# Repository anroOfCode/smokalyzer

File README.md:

smokalyzer
==========
Code and design files for a headset-connected device that can detect if you've been smoking.

Info
====
This project is based on the HiJack platform. It includes an interface board designed for use with an electrochemical gas sensor, 3D design files for the creation of an enclosure, and code for iOS and for the HiJack platform that allows for reading and calibration.

What You'll Find Here
=====================

Code for Use With TinyOS
------------------------
Code has been written to be used with the HiJack platform, installed with TinyOS. TinyOS is difficult to setup, but the process should look something like this:

- Check out version 2.1.1 from the TinyOS Subversion page
- Install it on your local machine, including tos-tools. (see documentation on their site)
- Check out the hijack-main code from the google code project and copy the directory structure such that it matches up with your tinyos main folder
- Build the apps using 'make hijack install miniprog bsl,/dev/ttyUSB0'

An iOS App That Displays CO Data
--------------------------------
This is one of my very, very first endeavors into iOS app making. The code is not clean but will hopefully be cleaned up over time. We've imported libHiJack from the HiJack project as well, which requires delicacy when it comes to using ARC. The app supports basic calibration and reading of the instrument. 

Board Design Files
------------------
The files will allow you to order more of the PCB. They have been produced using Eagle 6.3.0.

Enclosure Design Files
----------------------
These files can serve as a starting point for a professional enclosure. They can also be 3D prototyped by any 3D lab for prototype enclosures. 

Questions?
==========
Feel free to contact me with questions. Responses are not guaranteed.

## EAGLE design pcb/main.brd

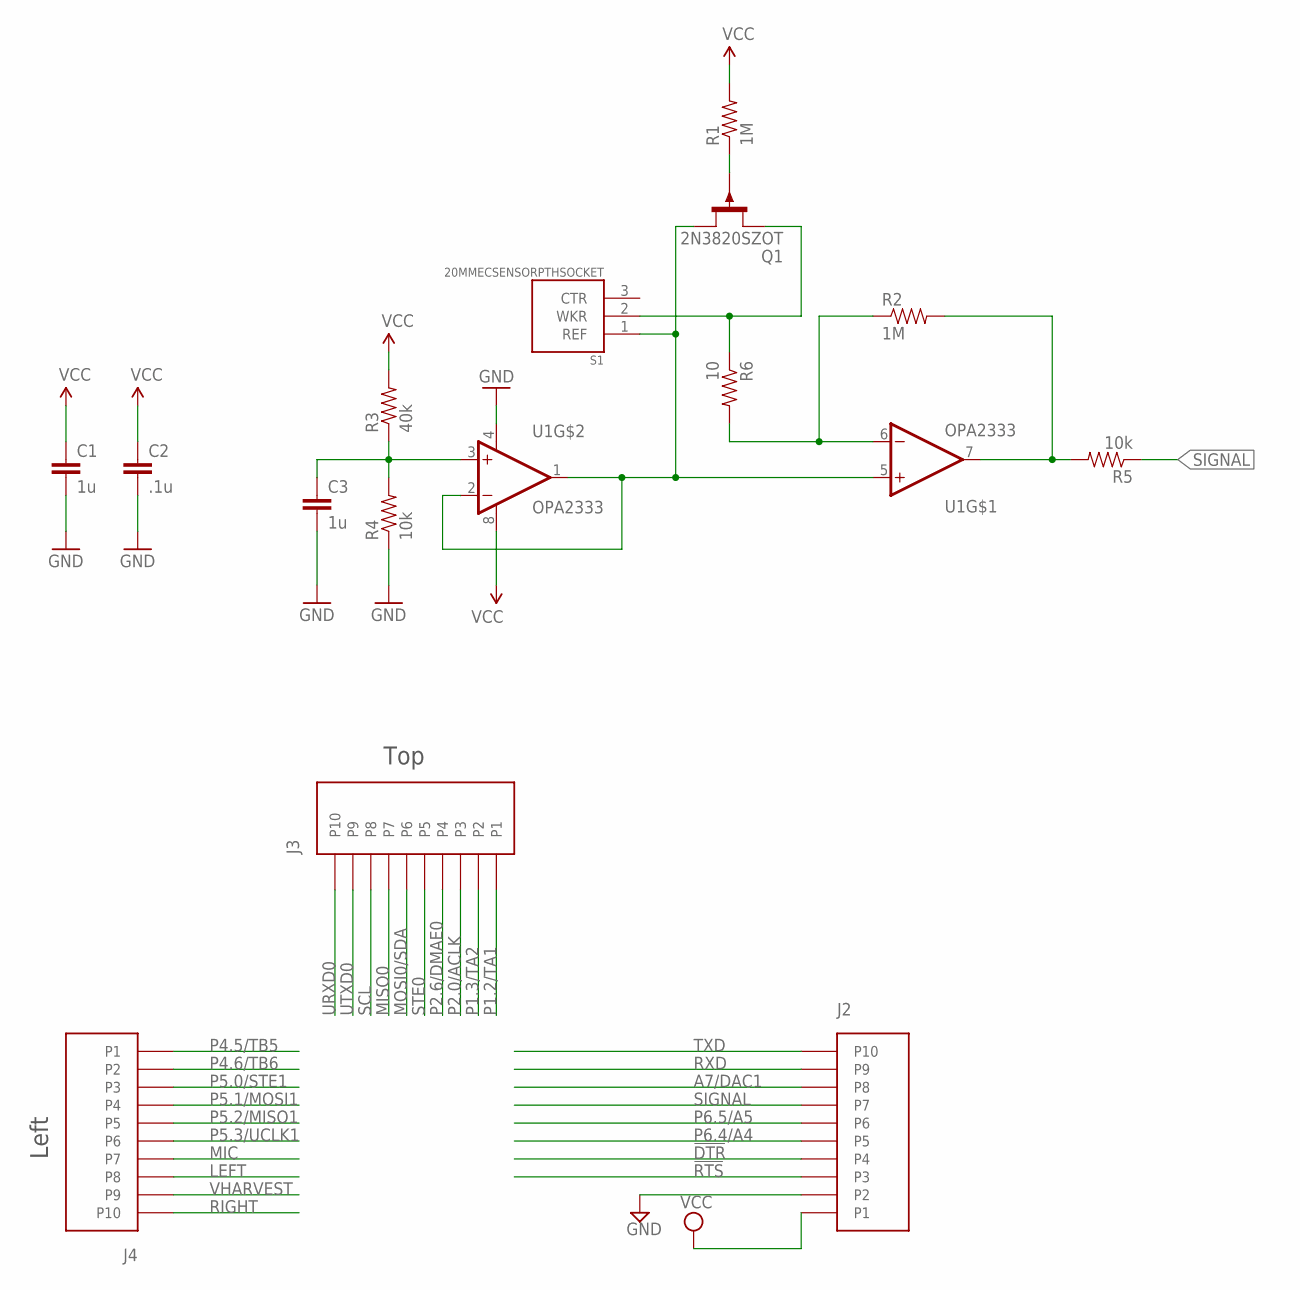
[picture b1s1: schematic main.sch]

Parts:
C1, C3: 1u; 0603-CAP
C2: .1u; 0603-CAP
J2, J3, J4: HEADER10POS; 10PIN2MMHEADER
Q1: 2N3820SZOT; SOT23-3
R1, R2: 1M; 0603-RES
R3: 40k; 0603-RES
R4, R5: 10k; 0603-RES
R6: 10; 0603-RES
S1: 20MMECSENSORPTHSOCKET; 20MMSENSOR
U1: OPA2333; SOIC

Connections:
!DTR: J2.P4
!RTS: J2.P3
A7/DAC1: J2.P8
GND: C1.2, C2.2, C3.2, J2.P2, R4.1, U1.4 (V-)
LEFT: J4.P8
MIC: J4.P7
MISO0: J3.P7
MOSI0/SDA: J3.P6
unnamed: Q1.1 (D), R6.1, S1.2 (WKR)
unnamed: R2.2, R5.2, U1.7 (OUT)
unnamed: R2.1, R6.2, U1.6 (-IN)
unnamed: Q1.3 (G), R1.1
P1.2/TA1: J3.P1
P1.3/TA2: J3.P2
P2.0/ACLK: J3.P3
P2.6/DMAE0: J3.P4
P4.5/TB5: J4.P1
P4.6/TB6: J4.P2
P5.0/STE1: J4.P3
P5.1/MOSI1: J4.P4
P5.2/MISO1: J4.P5
P5.3/UCLK1: J4.P6
P6.4/A4: J2.P5
P6.5/A5: J2.P6
RIGHT: J4.P10
RXD: J2.P9
SCL: J3.P8
SIGNAL: J2.P7, R5.1
STE0: J3.P5
TXD: J2.P10
URXD0: J3.P10
UTXD0: J3.P9
VCC: C1.1, C2.1, J2.P1, R1.2, R3.2, U1.8 (V+)
VHARVEST: J4.P9
VREF: Q1.2 (S), S1.1 (REF), U1.1 (OUT), U1.2 (-IN), U1.5 (+IN)
WHATEV: C3.1, R3.1, R4.2, U1.3 (+IN)

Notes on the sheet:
Left
Top

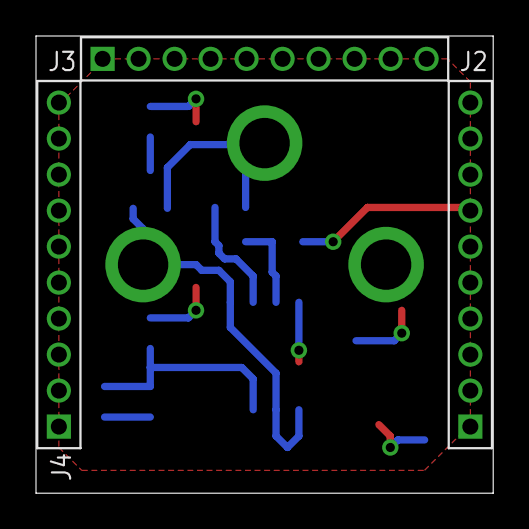
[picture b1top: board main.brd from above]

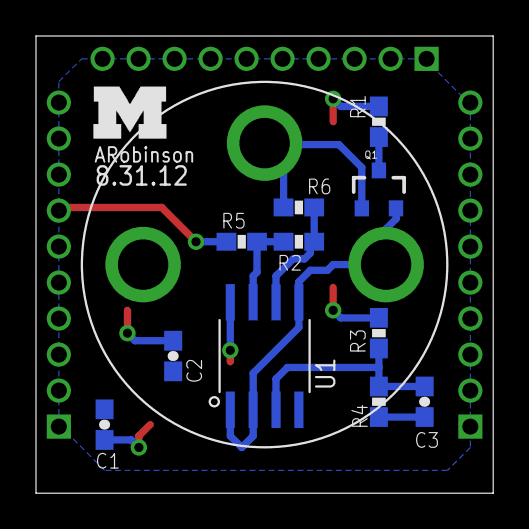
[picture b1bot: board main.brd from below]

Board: 2 copper layers, 25.4 x 25.4 mm, 16 parts (12 on the bottom side), 9 nets.

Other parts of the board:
U$1: BLOCK-M

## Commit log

2012-10-24 Added some information to the README
2012-10-24 Added cleaned up TinyOS code to project, working on new ADC sampling algorithm
2012-10-29 Fixed, using TinyOS v2.1.1 solves many of the issues
2012-10-29 Cleaned up the TinyOS source, out for now
2012-10-29 Added enclosure design files.
2012-10-30 Added initial iOS application skeleton
2012-10-30 Added internal flash storage stuff and the Makefile. Internal flash writing is currently not working.
2012-10-30 Working x-code project. It isnt pretty but it works darnit.
2012-10-30 Rewrote InternalFlash to not suck
2012-10-30 added receive state machine
2012-10-30 added receive processing checksum and write command.
2012-10-30 wrote test code to write device EEPROM and made interface for iOS app.
2012-10-30 working eeprom storage of calibration data
2012-10-30 updates to iOS application. almost working
2012-10-30 fixed thread synchronization problem. working iOS app now
2012-10-30 Added pcb design files to project.
2012-10-31 fixed a buffer overflow error
2012-10-31 Updating readme.
2012-11-03 Added instructions for use and photos
2012-11-04 refactoring part 1
2012-11-04 refactored signal generating function
2012-11-04 more refactoring
2012-11-04 refactoring 1 of encode function
2012-11-04 much better encoding function
2012-11-13 adding support for screen always on
